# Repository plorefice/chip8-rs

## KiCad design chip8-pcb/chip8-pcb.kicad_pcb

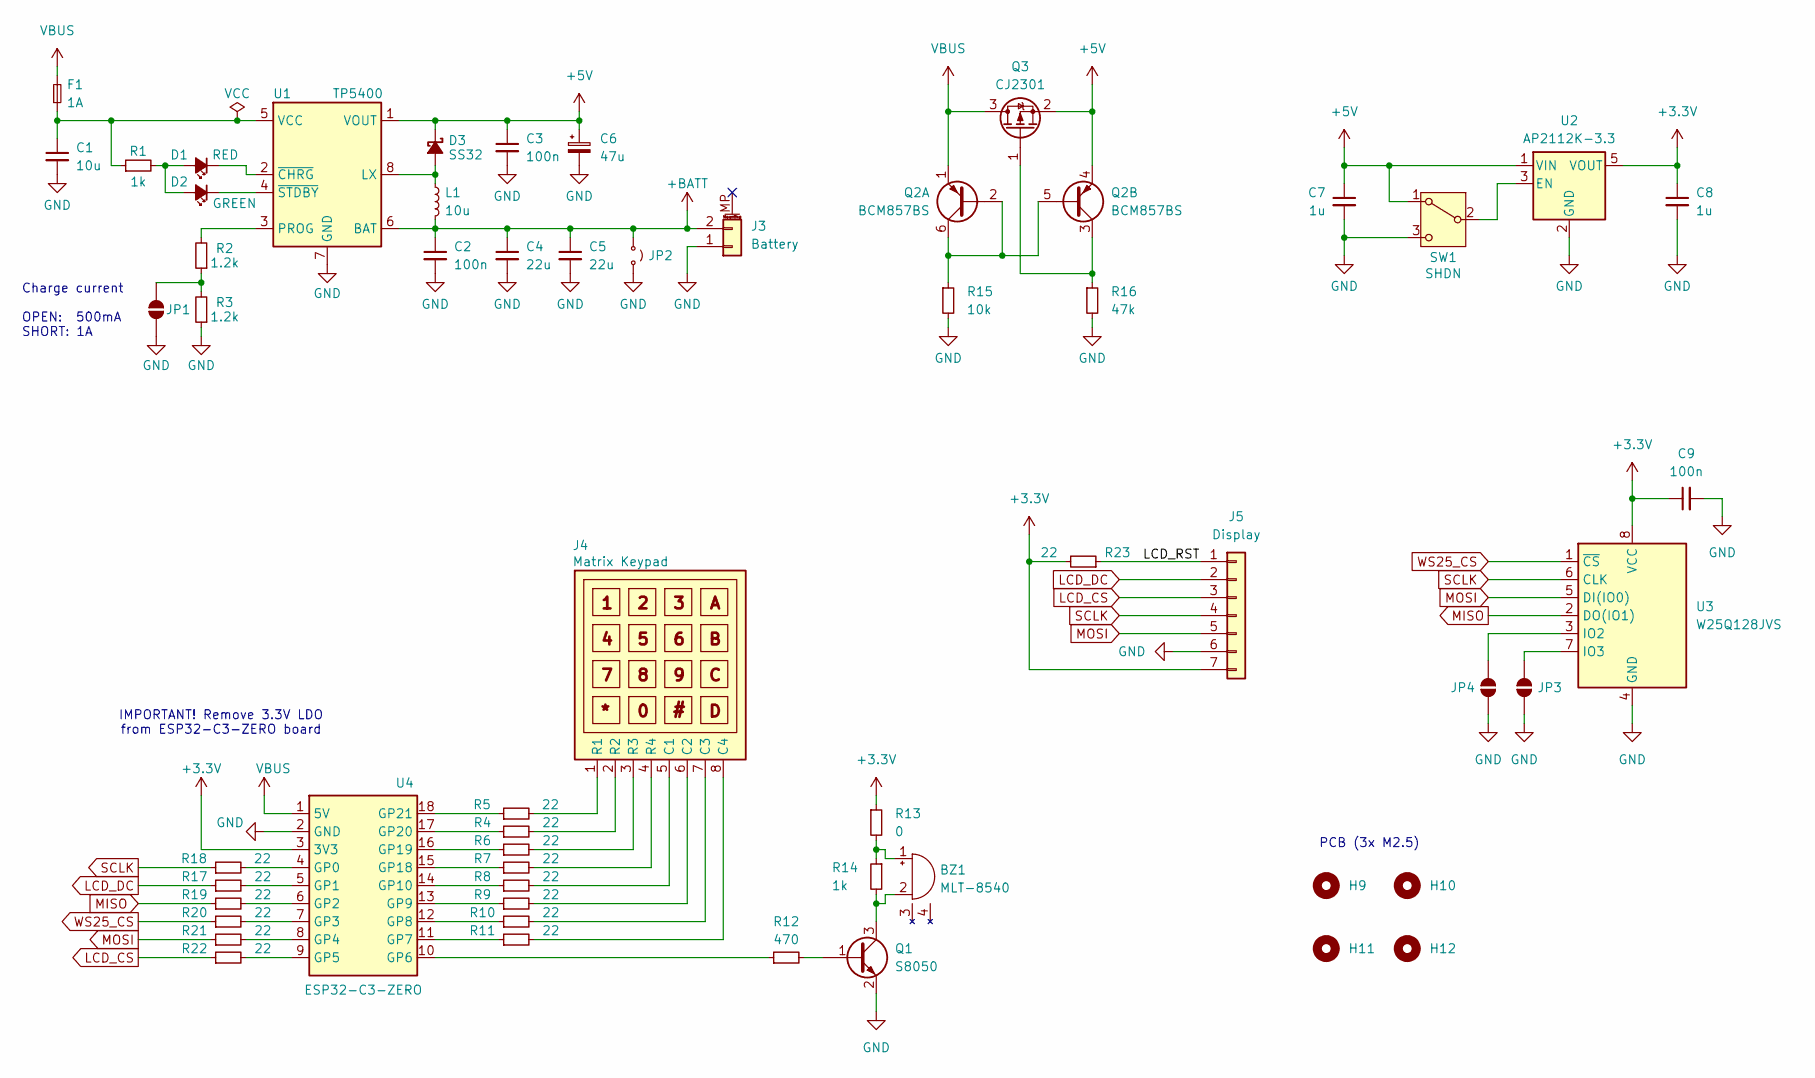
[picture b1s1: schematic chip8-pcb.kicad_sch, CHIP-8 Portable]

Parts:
BZ1: MLT-8540; LCSC Part Number C95300
C1: 10u; C_0603_1608Metric; LCSC Part Number C96446
C2, C3, C9: 100n; C_0603_1608Metric; LCSC Part Number C14663
C4, C5: 22u; C_0603_1608Metric; LCSC Part Number C59461
C6: 47u; CP_Elec_6.3x5.4; LCSC Part Number C72521
C7, C8: 1u; C_0603_1608Metric; LCSC Part Number C15849
D1: RED; LED_0805_2012Metric; LCSC Part Number C84256
D2: GREEN; LED_0805_2012Metric; LCSC Part Number C2297
D3: SS32; D_SMA; LCSC Part Number C34897
F1: 1A; Fuse_0603_1608Metric; LCSC Part Number C151139
H9, H10, H11, H12: MountingHole_2.2mm_M2
J3: Battery; BOOMELE_PH-2P_1x2P_P2.00mm_Horizontal; LCSC Part Number C47647
J4: Matrix Keypad; PinSocket_1x08_P2.54mm_Horizontal
J5: Display; PinHeader_1x07_P2.54mm_Horizontal
JP1, JP2, JP3, JP4: SolderJumper-2_P1.3mm_Open_RoundedPad1.0x1.5mm
L1: 10u; L_Sunlord_SWPA4030S; LCSC Part Number C5363814
Q1: S8050; SOT-23; LCSC Part Number C2146
Q2: BCM857BS; SOT-363_SC-70-6; LCSC Part Number C105896
Q3: CJ2301; SOT-23; LCSC Part Number C8547
R1, R14: 1k; R_0603_1608Metric; LCSC Part Number C21190
R2, R3: 1.2k; R_0603_1608Metric; LCSC Part Number C22765
R4, R5, R6, R7, R8, R9, R10, R11, R17, R18, R19, R20, R21, R22, R23: 22; R_0603_1608Metric; LCSC Part Number C23345
R12: 470; R_0603_1608Metric; LCSC Part Number C23179
R13: 0; R_0603_1608Metric; LCSC Part Number C21189
R15: 10k; R_0603_1608Metric; LCSC Part Number C25804
R16: 47k; R_0603_1608Metric; LCSC Part Number C25819
SW1: SHDN; SW_SPDT_CK_JS102011SAQN; LCSC Part Number C221660
U1: TP5400; HTSOP-8-1EP_3.9x4.9mm_P1.27mm_EP2.4x3.2mm_ThermalVias; LCSC Part Number C2891434
U2: AP2112K-3.3; SOT-23-5; LCSC Part Number C51118
U3: W25Q128JVS; SOIC-8_5.23x5.23mm_P1.27mm; LCSC Part Number C97521
U4: ESP32-C3-ZERO; WaveShare_ESP32-C3-ZERO

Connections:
+3.3V: C8.1, C9.1, J5.7, R13.1, R23.2, U2.5 (VOUT), U3.8 (VCC), U4.3 (3V3)
+5V: C3.1, C6.1, C7.1, D3.1 (K), Q2.4 (E2), Q3.2 (S), SW1.1 (A), U1.1 (VOUT), U2.1 (VIN)
+BATT: C2.1, C4.1, C5.1, J3.2, JP2.1 (A), L1.2, U1.6 (BAT)
/LCD_RST: J5.1, R23.1
GND: C1.2, C2.2, C3.2, C4.2, C5.2, C6.2, C7.2, C8.2, C9.2, J3.1, J5.6, JP1.1 (A), JP2.2 (B), JP3.1 (A), JP4.1 (A), Q1.2 (E), R3.1, R15.2, R16.2, SW1.3 (C), U1.7 (GND), U1.9 (GND), U2.2 (GND), U3.4 (GND), U4.2 (GND)
LCD_CS: J5.3, R22.1
LCD_DC: J5.2, R17.1
MISO: R19.1, U3.2 (DO(IO1))
MOSI: J5.5, R21.1, U3.5 (DI(IO0))
unnamed: BZ1.1 (+), R13.2, R14.1
unnamed: BZ1.2 (-), Q1.3 (C), R14.2
unnamed: D1.2 (A), D2.2 (A), R1.2
unnamed: D1.1 (K), U1.2 (~CHRG)
unnamed: D2.1 (K), U1.4 (~STDBY)
unnamed: D3.2 (A), L1.1, U1.8 (LX)
unnamed: J4.6 (C2), R9.2
unnamed: J4.7 (C3), R10.2
unnamed: J4.8 (C4), R11.2
unnamed: J4.1 (R1), R5.2
unnamed: J4.2 (R2), R4.2
unnamed: J4.3 (R3), R6.2
unnamed: J4.4 (R4), R7.2
unnamed: J4.5 (C1), R8.2
unnamed: JP1.2 (B), R2.1, R3.2
unnamed: JP3.2 (B), U3.7 (IO3)
unnamed: JP4.2 (B), U3.3 (IO2)
unnamed: Q1.1 (B), R12.2
unnamed: Q2.2 (B1), Q2.5 (B2), Q2.6 (C1), R15.1
unnamed: Q2.3 (C2), Q3.1 (G), R16.1
unnamed: SW1.2 (B), U2.3 (EN)
unnamed: R2.2, U1.3 (PROG)
unnamed: C1.1, F1.1, R1.1, U1.5 (VCC)
unnamed: R18.2, U4.4 (GP0)
unnamed: R17.2, U4.5 (GP1)
unnamed: R19.2, U4.6 (GP2)
unnamed: R20.2, U4.7 (GP3)
unnamed: R21.2, U4.8 (GP4)
unnamed: R22.2, U4.9 (GP5)
unnamed: R12.1, U4.10 (GP6)
unnamed: R11.1, U4.11 (GP7)
unnamed: R10.1, U4.12 (GP8)
unnamed: R9.1, U4.13 (GP9)
unnamed: R8.1, U4.14 (GP10)
unnamed: R7.1, U4.15 (GP18)
unnamed: R6.1, U4.16 (GP19)
unnamed: R4.1, U4.17 (GP20)
unnamed: R5.1, U4.18 (GP21)
SCLK: J5.4, R18.1, U3.6 (CLK)
VBUS: F1.2, Q2.1 (E1), Q3.3 (D), U4.1 (5V)
WS25_CS: R20.1, U3.1 (~CS)

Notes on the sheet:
PCB (3x M2.5)
IMPORTANT! Remove 3.3V LDO from ESP32-C3-ZERO board
Charge current OPEN: 500mA SHORT: 1A

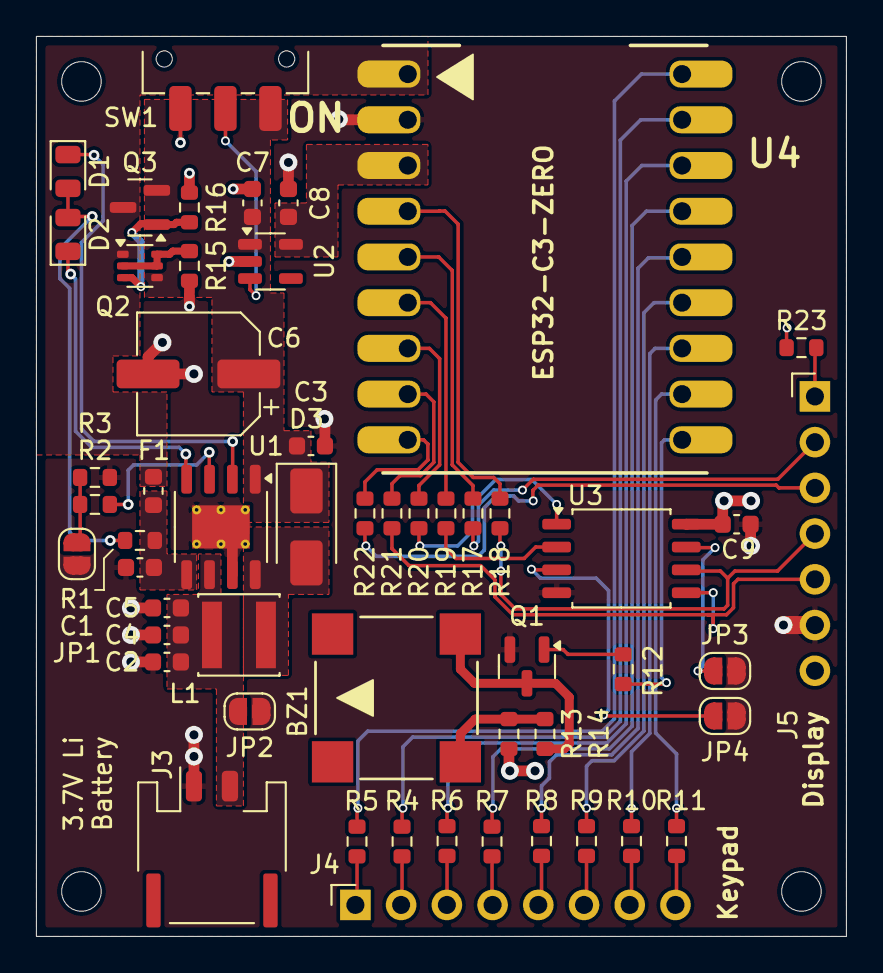
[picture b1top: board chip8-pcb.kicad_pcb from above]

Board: 4 copper layers, 45.0 x 50.0 mm, 57 parts (0 on the bottom side), 50 nets.

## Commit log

2019-01-18 Initial implementation (w/o input support)
2019-01-18 Switch to cargo workspaces
2019-01-18 Better error handling
2019-01-18 Add keypad handling
2019-01-18 Fix minor issues
2019-01-19 Clippy pass
2022-06-13 cargo: update dependencies
2022-06-13 chip8: core: remove redundant slice
2024-05-28 chip8: fix flags behavior
2024-05-28 chip8: quirks
2024-06-03 chip8-esp32: project skeleton
2024-06-03 chip8: switch to no_std
2024-06-03 chip8-esp32: cpu loop stub
2024-06-04 chip8-esp32: graphics
2024-06-04 Workspace fuckery
2024-06-04 chip8-esp32: 128x64 screen
2024-06-04 chip8-esp32: precise timing
2024-06-04 pcb: project stub
2024-06-08 chip8-pcb: final v1 version
2024-06-11 chip8-pcb: final v2 version
2024-06-12 case: initial version
2024-06-12 pcb: move battery and display connectors
2024-06-12 case: import pcb step model
2024-06-12 case: import keypad and oled step models
2024-06-12 case: import lipo battery model
